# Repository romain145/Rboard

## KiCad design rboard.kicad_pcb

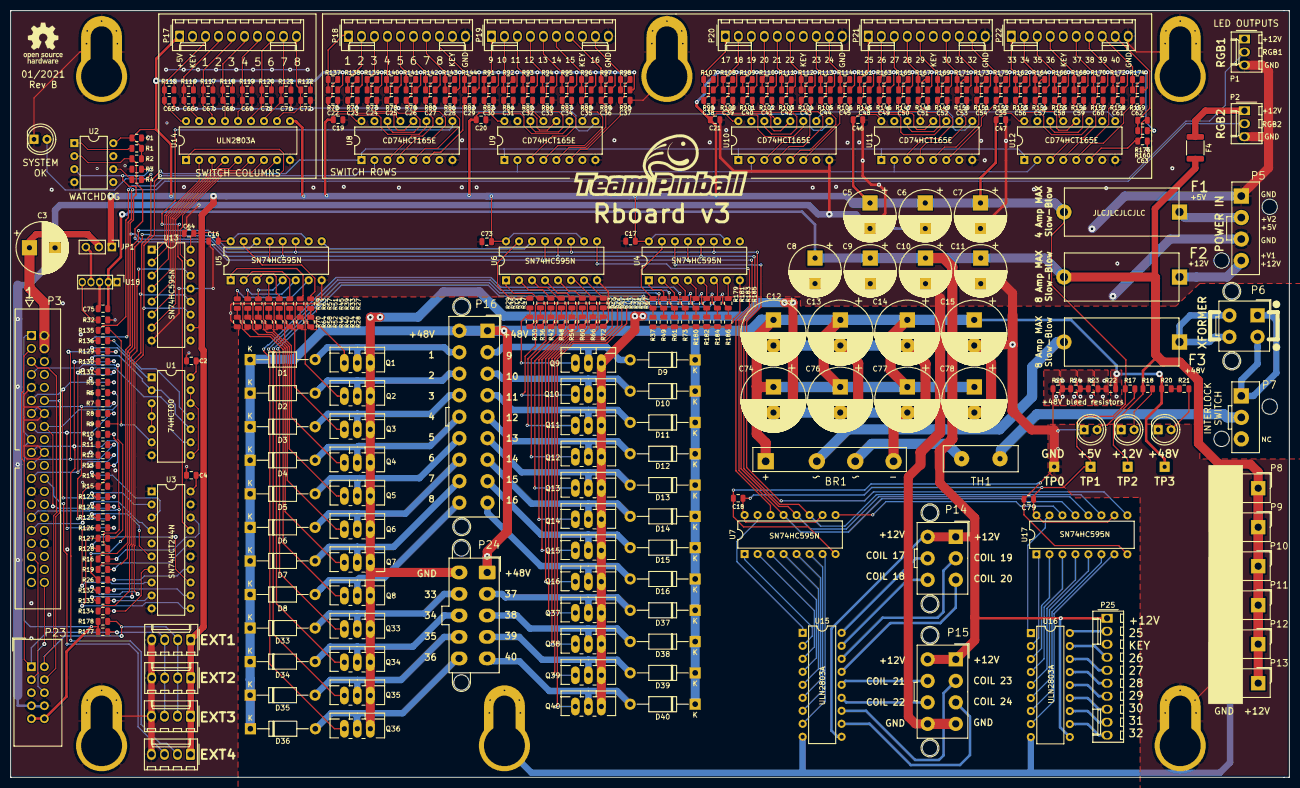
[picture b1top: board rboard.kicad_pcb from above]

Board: 2 copper layers, 249.9 x 149.9 mm, 377 parts (1 on the bottom side), 281 nets.

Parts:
BR1: GBK15B
C1, C2, C4, C16, C17, C18, C19, C20, C21, C46, C47, C64, C73, C79: 100nF; C_0805_2012Metric
C3, C5, C6, C7, C8, C9, C10, C11: 470u 25V; CP_Radial_D10.0mm_P5.00mm
C12, C13, C14, C15, C74, C76, C77, C78: 470u 63V; CP_Radial_D12.5mm_P5.00mm
C22, C23, C24, C25, C26, C27, C28, C29, C30, C31, C32, C33, C34, C35, C36, C37, C38, C39, C40, C41, C42, C43, C44, C45, C48, C49, C50, C51, C52, C53, C54, C55, C56, C57, C58, C59, C60, C61, C62, C63, C65, C66, C67, C68, C69, C70, C71, C72: 1nF; C_0805_2012Metric
C75: 10uF 16V; C_0805_2012Metric
D1, D2, D3, D4, D5, D6, D7, D8, D9, D10, D11, D12, D13, D14, D15, D16, D33, D34, D35, D36, D37, D38, D39, D40: SR1100; D_DO-41_SOD81_P12.70mm_Horizontal
EXT1, EXT2, EXT3, EXT4: Header 01x04; Molex_KK-254_AE-6410-04A_1x04_P2.54mm_Vertical
F1: 4A SB; HTC-100M
F2, F3: 6.3A SB; HTC-100M
F4: 0R; R_1812_4532Metric
JP1: Jumper_3_Bridged12; PinHeader_1x03_P2.54mm_Vertical
LED1, LED2, LED3, LED4: Green; LED_D5.0mm
LOGO1: TeamPinball; logo_team_pinball
LOGO2: OSHW; OSHW-Logo_7.5x8mm_SilkScreen
LOGO3: WEEE; WEEE-Logo_4.2x6mm_SilkScreen
NT1: net-tie; NET-TIE_DOUBLE
P1, P2: Header 01x03; Molex_KK-254_AE-6410-03A_1x03_P2.54mm_Vertical
P3: RaspberryPi; HE10-40
P5: PSU 12V5V; Mini-Fit_4W_single
P6: XFormer; Mini-Fit_4W
P7: Interlock SW; Mini-Fit_3W_single
P8, P9, P10, P11, P12, P13: Mini-Fit_2W
P14: Mini-Fit_6W
P15: Mini-Fit_8W
P16: Mini-Fit_18W
P17, P18, P19, P20, P21, P22, P25: Header 01x10; Molex_KK-254_AE-6410-10A_1x10_P2.54mm_Vertical
P23: PCM; IDC-Header_2x05_P2.54mm_Vertical
P24: Molex_Mini-Fit_Jr_5566-10A2_2x05_P4.20mm_Vertical; Mini-Fit_10W
Q1, Q2, Q3, Q4, Q5, Q6, Q7, Q8, Q9, Q10, Q11, Q12, Q13, Q14, Q15, Q16, Q33, Q34, Q35, Q36, Q37, Q38, Q39, Q40: IRL540; TO-220_123
R1, R2, R3, R5, R6, R7, R8, R9, R10, R11, R12, R13, R20, R21, R28, R30, R34, R36, R37, R40, R42, R46, R48, R49, R52, R54, R58, R60, R61, R64, R66, R70, R72, R73, R75, R76, R77, R78, R79, R80, R81, R82, R83, R84, R85, R86, R87, R88, R89, R90, R99, R100, R101, R102, R103, R104, R105, R106, R115, R116, R117, R118, R119, R120, R121, R122, R145, R146, R147, R148, R149, R150, R151, R152, R153, R154, R155, R156, R157, R158, R159, R160, R177, R178, R180, R182, R184, R186: 4.7k; R_0805_2012Metric
R4, R17, R22, R23, R24, R25, R91, R92, R93, R94, R95, R96, R97, R98, R107, R108, R109, R110, R111, R112, R113, R114, R137, R138, R139, R140, R141, R142, R143, R144, R161, R162, R163, R164, R165, R166, R167, R168, R169, R170, R171, R172, R173, R174, R175, R176: 1k; R_0805_2012Metric
R14, R15, R18: 2.2k; R_0805_2012Metric
R16, R19, R26, R27, R29, R31, R33, R35, R39, R41, R43, R45, R47, R51, R53, R55, R57, R59, R63, R65, R67, R69, R71, R123, R124, R125, R126, R127, R128, R129, R130, R131, R132, R133, R134, R135, R136, R179, R181, R183, R185: 100R; R_0805_2012Metric
R32: 261R; R_0805_2012Metric
SCR1, SCR2, SCR3, SCR4, SCR5, SCR6: Screw; 4mm-key-hole
TH1: B57237S0259M; Thermistor_D15mm_P7.50mm
TP0: TEST; 1test_pad
TP1: 5V Test Point; 1test_pad
TP2: 12V Test Point; 1test_pad
TP3: 48V Test Point; 1test_pad
U1: 74HCT00; DIP-14_W7.62mm
U2: ATTINY85-20PU; DIP-8_W7.62mm
U3: SN74HCT244N; DIP-20_W7.62mm
U4, U5, U6, U7, U13, U17: SN74HC595N; DIP-16_W7.62mm
U8, U9, U10, U11, U12: CD74HCT165E; DIP-16_W7.62mm
U14, U15, U16: ULN2803A; DIP-18_W7.62mm
U18: OKR-T/3-W12-C; OKR-T-3-W12-C

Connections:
+3V3: P3.1, P3.17, P23.9, P23.10, R177.1, R178.1
+5V: C3.1, JP1.2, P3.2, P3.4
+12V: C8.1, C9.1, C10.1, C11.1, C75.1, F2.2, F4.2, P8.1, P9.1, P10.1, P11.1, P12.1, P13.1, P14.1, P14.4, P15.1, P15.5, P25.1, R18.1, TP2.1, U15.10, U16.10, U18.2
+12V_LED: F4.1, P1.1, P2.1
+48V: BR1.1, C12.1, C13.1, C14.1, C15.1, C74.1, C76.1, C77.1, C78.1, D1.1, D2.1, D3.1, D4.1, D5.1, D6.1, D7.1, D8.1, D9.1, D10.1, D11.1, D12.1, D13.1, D14.1, D15.1, D16.1, D33.1, D34.1, D35.1, D36.1, D37.1, D38.1, D39.1, D40.1, P16.1, P16.10, P24.1, R20.1, R22.2, TP3.1
/12v outputs/CO17: U7.15, U15.1
/12v outputs/CO18: U7.1, U15.2
/12v outputs/CO19: U7.2, U15.3
/12v outputs/CO20: U7.3, U15.4
/12v outputs/CO21: U7.4, U15.5
/12v outputs/CO22: U7.5, U15.6
/12v outputs/CO23: U7.6, U15.7
/12v outputs/CO24: U7.7, U15.8
/12v outputs/CO25: U16.1, U17.15
/12v outputs/CO26: U16.2, U17.1
/12v outputs/CO27: U16.3, U17.2
/12v outputs/CO28: U16.4, U17.3
/12v outputs/CO29: U16.5, U17.4
/12v outputs/CO30: U16.6, U17.5
/12v outputs/CO31: U16.7, U17.6
/12v outputs/CO32: U16.8, U17.7
/12v outputs/COIL_17: P14.5, U15.18
/12v outputs/COIL_18: P14.6, U15.17
/12v outputs/COIL_19: P14.2, U15.16
/12v outputs/COIL_20: P14.3, U15.15
/12v outputs/COIL_21: P15.6, U15.14
/12v outputs/COIL_22: P15.7, U15.13
/12v outputs/COIL_23: P15.2, U15.12
/12v outputs/COIL_24: P15.3, U15.11
/12v outputs/COIL_25: P25.2, U16.18
/12v outputs/COIL_26: P25.4, U16.17
/12v outputs/COIL_27: P25.5, U16.16
/12v outputs/COIL_28: P25.6, U16.15
/12v outputs/COIL_29: P25.7, U16.14
/12v outputs/COIL_30: P25.8, U16.13
/12v outputs/COIL_31: P25.9, U16.12
/12v outputs/COIL_32: P25.10, U16.11
/12v outputs/COOUT17-32: U6.9, U7.14
/12v outputs/COOUT33-40: U4.14, U17.9
/BCLK_3V3: P3.12, P23.4
/COCLK_3V3: P3.16, R6.2, R124.2
/COCLK_5V: R19.1, U4.11, U5.11, U6.11, U7.11, U17.11
/COLATCH_3V3: P3.13, R7.2, R125.2
/COLATCH_5V: R3.2, R26.1, U2.3, U4.12, U5.12, U6.12, U7.12, U17.12
/COOUT_3V3: P3.11, R5.2, R123.2
/COOUT_5V: R16.1, U5.14
/DOUT_3V3: P3.40, P23.6
/EXT4_3V3: EXT4.3, P3.24
/LEDRGB1: P1.2, R135.1
/LEDRGB2: P2.2, R136.1
/LEDRGB_3V3: EXT4.2, P3.19, R13.2, R130.2
/LRCK_3V3: P3.35, P23.3
/RGB1_EN_3V3: P3.21, R11.2, R129.2
/RGB2_EN_3V3: P3.23, R12.2, R131.2
/SCL_3V3: EXT1.2, EXT2.2, EXT3.2, P3.5, P23.2, R178.2
/SDA_3V3: EXT1.3, EXT2.3, EXT3.3, P3.3, P23.1, R177.2
/SWCLK_3V3: P3.15, R8.2, R126.2
/SWCLK_5V: R132.1, U8.2, U9.2, U10.2, U11.2, U12.2, U13.11
/SWIN_3V3: P3.31, R14.2, R15.1
/SWIN_5V: U3.17, U8.9
/SWLATCH_3V3: P3.7, R9.2, R127.2
/SWLATCH_5V: R133.1, U8.1, U9.1, U10.1, U11.1, U12.1, U13.12
/SWOUT_3V3: P3.29, R10.2, R128.2
/SWOUT_5V: R134.1, U13.14
/coils outputs/CO1: Q1.1, R27.1, R28.2
/coils outputs/CO2: Q2.1, R33.1, R34.2
/coils outputs/CO3: Q3.1, R39.1, R40.2
/coils outputs/CO4: Q4.1, R45.1, R46.2
/coils outputs/CO5: Q5.1, R51.1, R52.2
/coils outputs/CO6: Q6.1, R57.1, R58.2
/coils outputs/CO7: Q7.1, R63.1, R64.2
/coils outputs/CO8: Q8.1, R69.1, R70.2
/coils outputs/CO9: Q9.1, R29.1, R30.2
/coils outputs/CO10: Q10.1, R35.1, R36.2
/coils outputs/CO11: Q11.1, R41.1, R42.2
/coils outputs/CO12: Q12.1, R47.1, R48.2
/coils outputs/CO13: Q13.1, R53.1, R54.2
/coils outputs/CO14: Q14.1, R59.1, R60.2
/coils outputs/CO15: Q15.1, R65.1, R66.2
/coils outputs/CO16: Q16.1, R71.1, R72.2
/coils outputs/CO33: Q33.1, R31.1, R37.2
/coils outputs/CO34: Q34.1, R43.1, R49.2
/coils outputs/CO35: Q35.1, R55.1, R61.2
/coils outputs/CO36: Q36.1, R67.1, R73.2
/coils outputs/CO37: Q37.1, R179.1, R180.2
/coils outputs/CO38: Q38.1, R181.1, R182.2
/coils outputs/CO39: Q39.1, R183.1, R184.2
/coils outputs/CO40: Q40.1, R185.1, R186.2
/coils outputs/COIL_1: D1.2, P16.11, Q1.2
/coils outputs/COIL_2: D2.2, P16.12, Q2.2
/coils outputs/COIL_3: D3.2, P16.13, Q3.2
/coils outputs/COIL_4: D4.2, P16.14, Q4.2
/coils outputs/COIL_5: D5.2, P16.15, Q5.2
/coils outputs/COIL_6: D6.2, P16.16, Q6.2
/coils outputs/COIL_7: D7.2, P16.17, Q7.2
/coils outputs/COIL_8: D8.2, P16.18, Q8.2
/coils outputs/COIL_9: D9.2, P16.2, Q9.2
/coils outputs/COIL_10: D10.2, P16.3, Q10.2
/coils outputs/COIL_11: D11.2, P16.4, Q11.2
/coils outputs/COIL_12: D12.2, P16.5, Q12.2
/coils outputs/COIL_13: D13.2, P16.6, Q13.2
/coils outputs/COIL_14: D14.2, P16.7, Q14.2
/coils outputs/COIL_15: D15.2, P16.8, Q15.2
/coils outputs/COIL_16: D16.2, P16.9, Q16.2
/coils outputs/COIL_33: D33.2, P24.7, Q33.2
/coils outputs/COIL_34: D34.2, P24.8, Q34.2
/coils outputs/COIL_35: D35.2, P24.9, Q35.2
/coils outputs/COIL_36: D36.2, P24.10, Q36.2
/coils outputs/COIL_37: D37.2, P24.2, Q37.2
/coils outputs/COIL_38: D38.2, P24.3, Q38.2
/coils outputs/COIL_39: D39.2, P24.4, Q39.2
/coils outputs/COIL_40: D40.2, P24.5, Q40.2
/power supply/35VAC_NTC: BR1.3, TH1.1
/power supply/35VAC_live: P6.1, P6.2, P7.1
/power supply/35VAC_return: P7.2, TH1.2
/power supply/+V1: F2.1, P5.4
/power supply/+V2: F1.1, P5.2
/power supply/Trim: R32.1, U18.5
/power supply/Vout: JP1.3, U18.4
/switch inputs/COL1: C65.1, P17.3, R115.1, U14.18
/switch inputs/COL2: C66.1, P17.4, R116.1, U14.17
/switch inputs/COL3: C67.1, P17.5, R117.1, U14.16
/switch inputs/COL4: C68.1, P17.6, R118.1, U14.15
/switch inputs/COL5: C69.1, P17.7, R119.1, U14.14
/switch inputs/COL6: C70.1, P17.8, R120.1, U14.13
/switch inputs/COL7: C71.1, P17.9, R121.1, U14.12
/switch inputs/COL8: C72.1, P17.10, R122.1, U14.11
/switch inputs/SW1: P18.1, R75.1, R137.2
/switch inputs/SW2: P18.2, R76.1, R138.2
/switch inputs/SW3: P18.3, R77.1, R139.2
/switch inputs/SW4: P18.4, R78.1, R140.2
/switch inputs/SW5: P18.5, R79.1, R141.2
/switch inputs/SW6: P18.6, R80.1, R142.2
/switch inputs/SW7: P18.7, R81.1, R143.2
/switch inputs/SW8: P18.8, R82.1, R144.2
/switch inputs/SW9: P19.1, R83.1, R91.2
/switch inputs/SW10: P19.2, R84.1, R92.2
/switch inputs/SW11: P19.3, R85.1, R93.2
/switch inputs/SW12: P19.4, R86.1, R94.2
/switch inputs/SW13: P19.5, R87.1, R95.2
/switch inputs/SW14: P19.6, R88.1, R96.2
/switch inputs/SW15: P19.7, R89.1, R97.2
/switch inputs/SW16: P19.9, R90.1, R98.2
/switch inputs/SW17: P20.1, R99.1, R107.2
/switch inputs/SW18: P20.2, R100.1, R108.2
/switch inputs/SW19: P20.3, R101.1, R109.2
/switch inputs/SW20: P20.4, R102.1, R110.2
/switch inputs/SW21: P20.5, R103.1, R111.2
/switch inputs/SW22: P20.6, R104.1, R112.2
/switch inputs/SW23: P20.8, R105.1, R113.2
/switch inputs/SW24: P20.9, R106.1, R114.2
/switch inputs/SW25: P21.1, R145.1, R161.2
/switch inputs/SW26: P21.2, R146.1, R163.2
/switch inputs/SW27: P21.3, R147.1, R165.2
/switch inputs/SW28: P21.4, R148.1, R167.2
/switch inputs/SW29: P21.5, R149.1, R169.2
/switch inputs/SW30: P21.7, R150.1, R171.2
/switch inputs/SW31: P21.8, R151.1, R173.2
/switch inputs/SW32: P21.9, R152.1, R175.2
/switch inputs/SW33: P22.1, R153.1, R162.2
/switch inputs/SW34: P22.2, R154.1, R164.2
/switch inputs/SW35: P22.3, R155.1, R166.2
/switch inputs/SW36: P22.4, R156.1, R168.2
/switch inputs/SW37: P22.6, R157.1, R170.2
/switch inputs/SW38: P22.7, R158.1, R172.2
/switch inputs/SW39: P22.8, R159.1, R174.2
/switch inputs/SW40: P22.9, R160.1, R176.2
/switch inputs/SW_S: U10.10, U11.9
/~: R2.1, U2.2, U4.13, U5.13, U6.13, U7.13, U17.13
GND: C1.2, C2.2, C3.2, C4.2, C5.2, C6.2, C7.2, C8.2, C9.2, C10.2, C11.2, C16.2, C17.2, C18.2, C19.2, C20.2, C21.2, C22.2, C23.2, C24.2, C25.2, C26.2, C27.2, C28.2, C29.2, C30.2, C31.2, C32.2, C33.2, C34.2, C35.2, C36.2, C37.2, C38.2, C39.2, C40.2, C41.2, C42.2, C43.2, C44.2, C45.2, C46.2, C47.2, C48.2, C49.2, C50.2, C51.2, C52.2, C53.2, C54.2, C55.2, C56.2, C57.2, C58.2, C59.2, C60.2, C61.2, C62.2, C63.2, C64.2, C65.2, C66.2, C67.2, C68.2, C69.2, C70.2, C71.2, C72.2, C73.2, C75.2, C79.2, EXT1.4, EXT2.4, EXT3.4, EXT4.4, LED1.1, LED2.1, LED3.1, LED4.1, NT1.1B, NT1.1F, P1.3, P2.3, P3.6, P3.9, P3.14, P3.20, P3.25, P3.30, P3.34, P3.39, P5.1, P5.3, P8.2, P9.2, P10.2, P11.2, P12.2, P13.2, P15.4, P15.8, P18.10, P19.10, P20.10, P21.10, P22.10, P23.7, P23.8, R3.1, R5.1, R6.1, R7.1, R8.1, R9.1, R10.1, R11.1, R12.1, R13.1, R15.2, R25.1, R28.1, R30.1, R32.2, R34.1, R36.1, R37.1, R40.1, R42.1, R46.1, R48.1, R49.1, R52.1, R54.1, R58.1, R60.1, R61.1, R64.1, R66.1, R70.1, R72.1, R73.1, R180.1, R182.1, R184.1, R186.1, SCR1.1, SCR2.1, SCR3.1, SCR4.1, SCR5.1, SCR6.1, TP0.1, U1.7, U2.4, U3.1, U3.10, U3.15, U3.19, U4.8, U5.8, U6.8, U7.8, U8.8, U8.15, U9.8, U9.15, U10.8, U10.15, U11.8, U11.15, U12.8, U12.15, U13.8, U13.13, U14.9, U15.9, U16.9, U17.8, U18.3
GNDPWR: BR1.4, C12.2, C13.2, C14.2, C15.2, C74.2, C76.2, C77.2, C78.2, NT1.2B, NT1.2F, P24.6, Q1.3, Q2.3, Q3.3, Q4.3, Q5.3, Q6.3, Q7.3, Q8.3, Q9.3, Q10.3, Q11.3, Q12.3, Q13.3, Q14.3, Q15.3, Q16.3, Q33.3, Q34.3, Q35.3, Q36.3, Q37.3, Q38.3, Q39.3, Q40.3
unnamed: BR1.2, F3.2
unnamed: C22.1, R137.1, U8.11
unnamed: C23.1, R138.1, U8.12
unnamed: C24.1, R139.1, U8.13
unnamed: C25.1, R140.1, U8.14
unnamed: C26.1, R141.1, U8.3
unnamed: C27.1, R142.1, U8.4
unnamed: C28.1, R143.1, U8.5
unnamed: C29.1, R144.1, U8.6
unnamed: C30.1, R91.1, U9.11
unnamed: C31.1, R92.1, U9.12
unnamed: C32.1, R93.1, U9.13
unnamed: C33.1, R94.1, U9.14
unnamed: C34.1, R95.1, U9.3
unnamed: C35.1, R96.1, U9.4
unnamed: C36.1, R97.1, U9.5
unnamed: C37.1, R98.1, U9.6
unnamed: C38.1, R107.1, U10.11
unnamed: C39.1, R108.1, U10.12
unnamed: C40.1, R109.1, U10.13
unnamed: C41.1, R110.1, U10.14
unnamed: C42.1, R111.1, U10.3
unnamed: C43.1, R112.1, U10.4
unnamed: C44.1, R113.1, U10.5
unnamed: C45.1, R114.1, U10.6
unnamed: C48.1, R161.1, U11.11
unnamed: C49.1, R163.1, U11.12
unnamed: C50.1, R165.1, U11.13
unnamed: C51.1, R167.1, U11.14
unnamed: C52.1, R169.1, U11.3
unnamed: C53.1, R171.1, U11.4
unnamed: C54.1, R173.1, U11.5
unnamed: C55.1, R175.1, U11.6
unnamed: C56.1, R162.1, U12.11
unnamed: C57.1, R164.1, U12.12
unnamed: C58.1, R166.1, U12.13
unnamed: C59.1, R168.1, U12.14
unnamed: C60.1, R170.1, U12.3
unnamed: C61.1, R172.1, U12.4
unnamed: C62.1, R174.1, U12.5
unnamed: C63.1, R176.1, U12.6
unnamed: F3.1, P6.3, P6.4
unnamed: LED1.2, R17.2
unnamed: LED2.2, R18.2
unnamed: LED3.2, R21.2
unnamed: LED4.2, R4.2
unnamed: R1.1, U2.1
unnamed: R4.1, U2.6
unnamed: R14.1, U3.3
unnamed: R16.2, U3.18
unnamed: R19.2, U3.16
unnamed: R20.2, R21.1
unnamed: R22.1, R23.2
unnamed: R23.1, R24.2
unnamed: R24.1, R25.2
unnamed: R26.2, U3.14
unnamed: R27.2, U5.15
unnamed: R29.2, U6.15
unnamed: R31.2, U4.15
unnamed: R33.2, U5.1
unnamed: R35.2, U6.1
unnamed: R39.2, U5.2
unnamed: R41.2, U6.2
unnamed: R43.2, U4.1
unnamed: R45.2, U5.3
unnamed: R47.2, U6.3
unnamed: R51.2, U5.4
unnamed: R53.2, U6.4
unnamed: R55.2, U4.2
unnamed: R57.2, U5.5
unnamed: R59.2, U6.5
unnamed: R63.2, U5.6
unnamed: R65.2, U6.6
unnamed: R67.2, U4.3
unnamed: R69.2, U5.7
unnamed: R71.2, U6.7
unnamed: R123.1, U3.2
unnamed: R124.1, U3.4
unnamed: R125.1, U3.6
unnamed: R126.1, U3.8
unnamed: R127.1, U3.11
unnamed: R128.1, U3.13
unnamed: R129.1, U1.1
unnamed: R130.1, U1.2, U1.10
unnamed: R131.1, U1.9
unnamed: R132.2, U3.12
unnamed: R133.2, U3.9
unnamed: R134.2, U3.7
unnamed: R135.2, U1.6
unnamed: R136.2, U1.11
unnamed: R179.2, U4.4
unnamed: R181.2, U4.5
unnamed: R183.2, U4.6
unnamed: R185.2, U4.7
unnamed: U1.3, U1.4, U1.5
unnamed: U1.8, U1.12, U1.13
unnamed: U5.9, U6.14
unnamed: U8.10, U9.9
unnamed: U9.10, U10.9
unnamed: U11.10, U12.9
unnamed: U13.1, U14.2
unnamed: U13.2, U14.3
unnamed: U13.3, U14.4
unnamed: U13.4, U14.5
unnamed: U13.5, U14.6
unnamed: U13.6, U14.7
unnamed: U13.7, U14.8
unnamed: U13.15, U14.1
unnamed: U7.9, U17.14
VCC: C1.1, C2.1, C4.1, C5.1, C6.1, C7.1, C16.1, C17.1, C18.1, C19.1, C20.1, C21.1, C46.1, C47.1, C64.1, C73.1, C79.1, EXT1.1, EXT2.1, EXT3.1, EXT4.1, F1.2, JP1.1, P17.1, R1.2, R2.2, R17.1, R75.2, R76.2, R77.2, R78.2, R79.2, R80.2, R81.2, R82.2, R83.2, R84.2, R85.2, R86.2, R87.2, R88.2, R89.2, R90.2, R99.2, R100.2, R101.2, R102.2, R103.2, R104.2, R105.2, R106.2, R115.2, R116.2, R117.2, R118.2, R119.2, R120.2, R121.2, R122.2, R145.2, R146.2, R147.2, R148.2, R149.2, R150.2, R151.2, R152.2, R153.2, R154.2, R155.2, R156.2, R157.2, R158.2, R159.2, R160.2, TP1.1, U1.14, U2.8, U3.20, U4.10, U4.16, U5.10, U5.16, U6.10, U6.16, U7.10, U7.16, U8.16, U9.16, U10.16, U11.16, U12.16, U13.10, U13.16, U14.10, U17.10, U17.16

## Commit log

2021-01-17 All 3D models added for 3d export
2021-01-18 Latest schematic export

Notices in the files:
rboard.kicad_pcb:
GNU GPL V3
